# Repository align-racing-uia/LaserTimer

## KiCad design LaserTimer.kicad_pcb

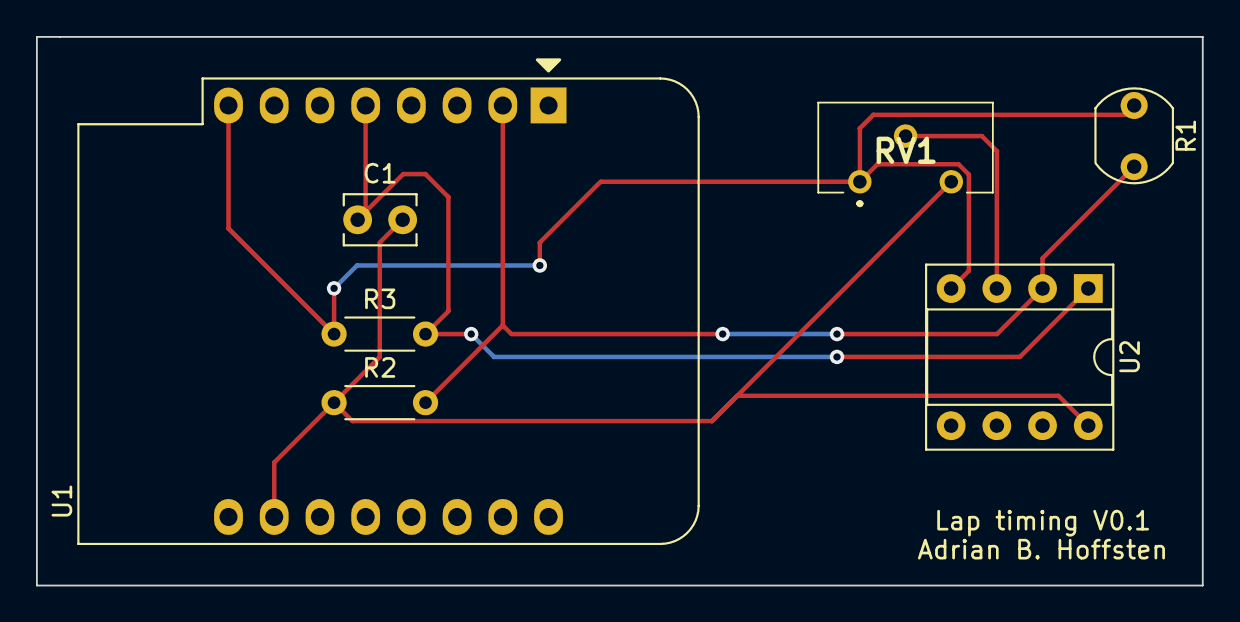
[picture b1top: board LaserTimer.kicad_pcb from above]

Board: 2 copper layers, 64.8 x 30.5 mm, 7 parts (0 on the bottom side), 5 nets.

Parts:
C1: 15pF; C_Disc_D3.8mm_W2.6mm_P2.50mm
R1: LDR07; R_LDR_5.1x4.3mm_P3.4mm_Vertical
R2: 10k; R_Axial_DIN0204_L3.6mm_D1.6mm_P5.08mm_Horizontal
R3: 1k; R_Axial_DIN0204_L3.6mm_D1.6mm_P5.08mm_Horizontal
RV1: R_Potentiometer; T93YB104KT20
U1: WeMos_D1_mini; WEMOS_D1_mini_light
U2: LM2903; DIP-8_W7.62mm_Socket

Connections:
+3.3V: R1.1, R3.1, RV1.1, U1.8 (3V3), U2.4 (GND)
/Sensor_Analog: R1.2, R2.2, U1.2 (A0), U2.2 (-)
/Sensor_Digital: C1.1, R3.2, U1.5 (MISO/D6), U2.1
GND: C1.2, R2.1, RV1.3, U1.10 (GND), U2.8 (VCC)
unnamed: RV1.2, U2.3 (+)

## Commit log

2022-09-15 Initial commit V0.1
